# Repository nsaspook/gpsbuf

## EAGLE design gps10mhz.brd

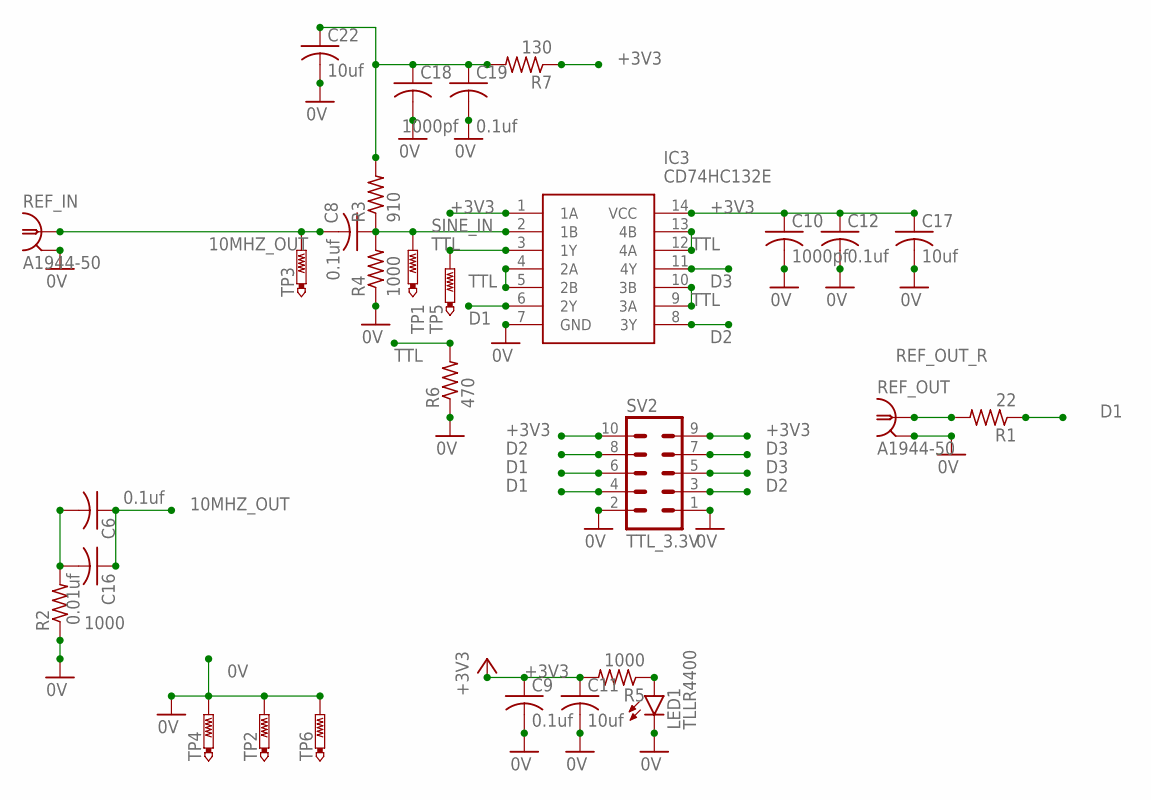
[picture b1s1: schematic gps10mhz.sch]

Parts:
C6, C8, C9, C12, C19: 0.1uf; C0805
C10, C18: 1000pf; C0805
C11, C17, C22: 10uf; C0805
C16: 0.01uf; C0805
IC3: CD74HC132E; DIP794W53P254L1930H508Q14N
LED1: TLLR4400; LED3MM
R1: 22; R1206
R2, R4, R5: 1000; R1206
R3: 910; R1206
R6: 470; R1206
R7: 130; R1206
REF_IN: A1944-50; A1944
REF_OUT: A1944-50; A1944
SV2: TTL_3.3V; MA05-2
TP1, TP2, TP3, TP4, TP5, TP6: PTR1PAD1-13; P1-13

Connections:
0V: C9.2, C10.2, C11.2, C12.2, C17.2, C18.2, C19.2, C22.2, IC3.7 (GND), LED1.K (C), R2.1, R4.1, R6.1, REF_IN.2, REF_IN.3 (2), REF_IN.4 (2), REF_IN.5 (2), REF_OUT.2, REF_OUT.3 (2), REF_OUT.4 (2), REF_OUT.5 (2), SV2.1, SV2.2, TP2.TP, TP4.TP, TP6.TP
10MHZ_OUT: C6.1, C8.2, C16.1, REF_IN.1, TP3.TP
+3V3: C9.1, C10.1, C11.1, C12.1, C17.1, IC3.1 (1A), IC3.14 (VCC), R5.2, R7.1, SV2.9, SV2.10
BIASV: C18.1, C19.1, C22.1, R3.2, R7.2
D1: IC3.6 (2Y), R1.1, SV2.4, SV2.6
D2: IC3.8 (3Y), SV2.3, SV2.8
D3: IC3.11 (4Y), SV2.5, SV2.7
unnamed: LED1.A, R5.1
OUT: C6.2, C16.2, R2.2
REF_OUT_R: R1.2, REF_OUT.1
SINE_IN: C8.1, IC3.2 (1B), R3.1, R4.2, TP1.TP
TTL: IC3.3 (1Y), IC3.4 (2A), IC3.5 (2B), IC3.9 (3A), IC3.10 (3B), IC3.12 (4A), IC3.13 (4B), R6.2, TP5.TP

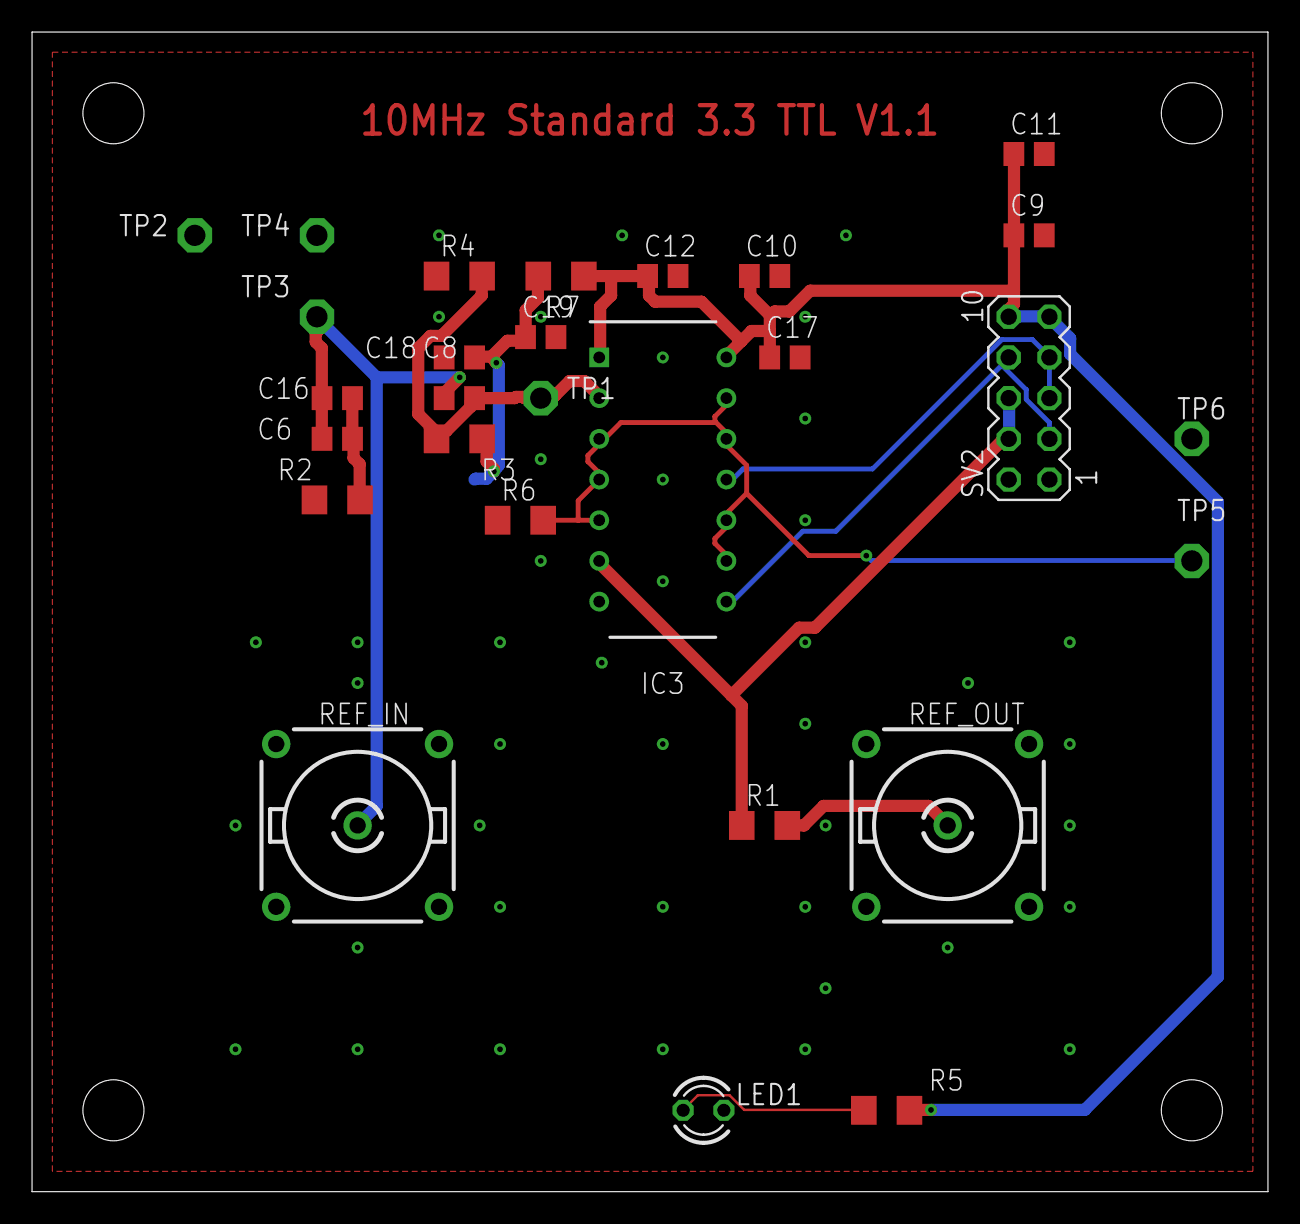
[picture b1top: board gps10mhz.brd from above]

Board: 2 copper layers, 77.1 x 72.4 mm, 29 parts (1 on the bottom side), 12 nets.

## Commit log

2025-01-26 3.3 digital only version
